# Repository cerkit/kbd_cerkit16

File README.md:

# kbd_cerkit16
 16 Key macro pad

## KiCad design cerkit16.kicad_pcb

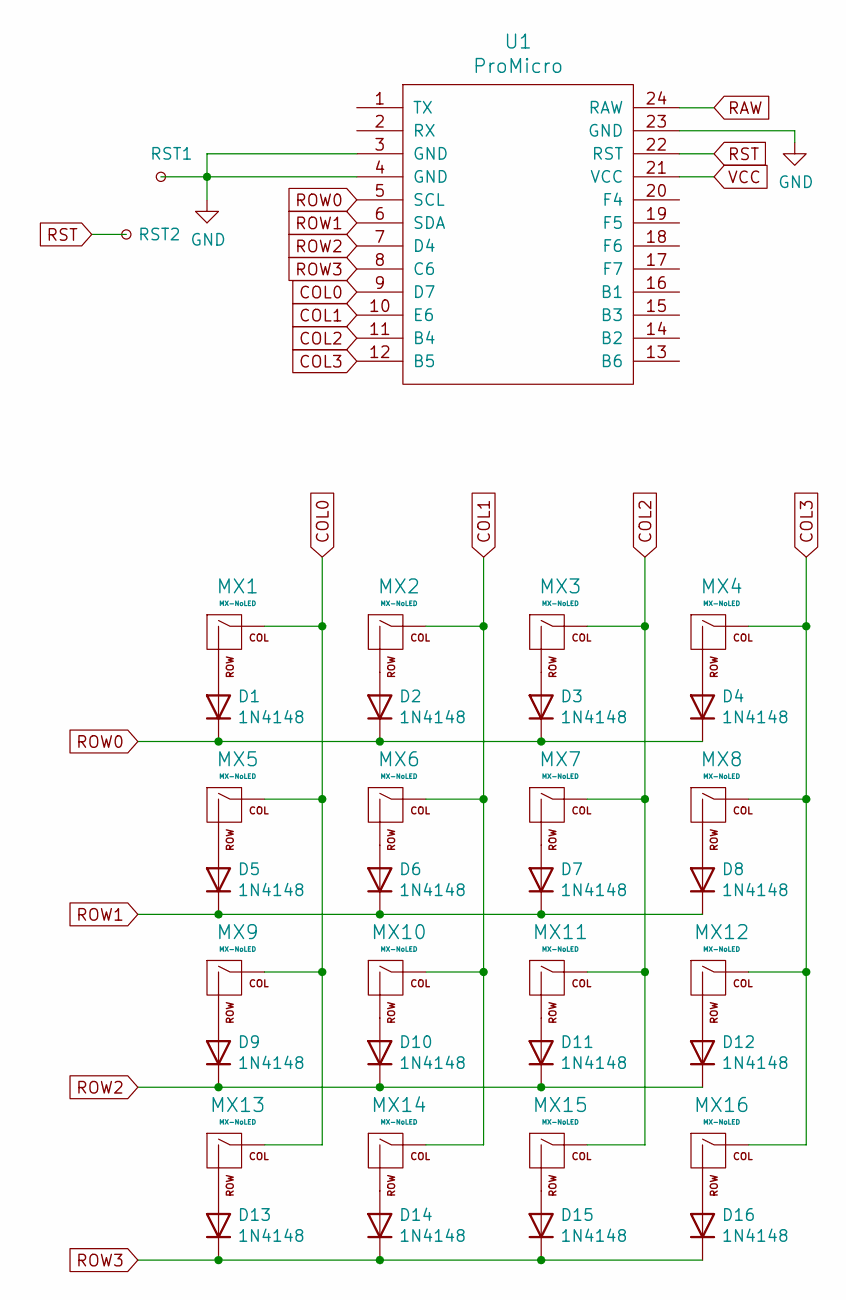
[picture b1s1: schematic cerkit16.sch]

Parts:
D1, D2, D3, D4, D5, D6, D7, D8, D9, D10, D11, D12, D13, D14, D15, D16: 1N4148; D_DO-35_SOD27_P7.62mm_Horizontal
MX1, MX2, MX3, MX4, MX5, MX6, MX7, MX8, MX9, MX10, MX11, MX12, MX13, MX14, MX15, MX16: MX-NoLED; MXOnly-1U-NoLED
RST1, RST2: TestPoint_Small; TestPoint_Pad_1.5x1.5mm
U1: ProMicro

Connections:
COL0: MX1.1 (COL), MX5.1 (COL), MX9.1 (COL), MX13.1 (COL), U1.9 (D7)
COL1: MX2.1 (COL), MX6.1 (COL), MX10.1 (COL), MX14.1 (COL), U1.10 (E6)
COL2: MX3.1 (COL), MX7.1 (COL), MX11.1 (COL), MX15.1 (COL), U1.11 (B4)
COL3: MX4.1 (COL), MX8.1 (COL), MX12.1 (COL), MX16.1 (COL), U1.12 (B5)
GND: RST1.1, U1.3 (GND), U1.4 (GND), U1.23 (GND)
unnamed: D1.2 (A), MX1.2 (ROW)
unnamed: D2.2 (A), MX2.2 (ROW)
unnamed: D3.2 (A), MX3.2 (ROW)
unnamed: D4.2 (A), MX4.2 (ROW)
unnamed: D5.2 (A), MX5.2 (ROW)
unnamed: D6.2 (A), MX6.2 (ROW)
unnamed: D7.2 (A), MX7.2 (ROW)
unnamed: D8.2 (A), MX8.2 (ROW)
unnamed: D9.2 (A), MX9.2 (ROW)
unnamed: D10.2 (A), MX10.2 (ROW)
unnamed: D11.2 (A), MX11.2 (ROW)
unnamed: D12.2 (A), MX12.2 (ROW)
unnamed: D13.2 (A), MX13.2 (ROW)
unnamed: D14.2 (A), MX14.2 (ROW)
unnamed: D15.2 (A), MX15.2 (ROW)
unnamed: D16.2 (A), MX16.2 (ROW)
RAW: U1.24 (RAW)
ROW0: D1.1 (K), D2.1 (K), D3.1 (K), D4.1 (K), U1.5 (SCL)
ROW1: D5.1 (K), D6.1 (K), D7.1 (K), D8.1 (K), U1.6 (SDA)
ROW2: D9.1 (K), D10.1 (K), D11.1 (K), D12.1 (K), U1.7 (D4)
ROW3: D13.1 (K), D14.1 (K), D15.1 (K), D16.1 (K), U1.8 (C6)
RST: RST2.1, U1.22 (RST)
VCC: U1.21 (VCC)

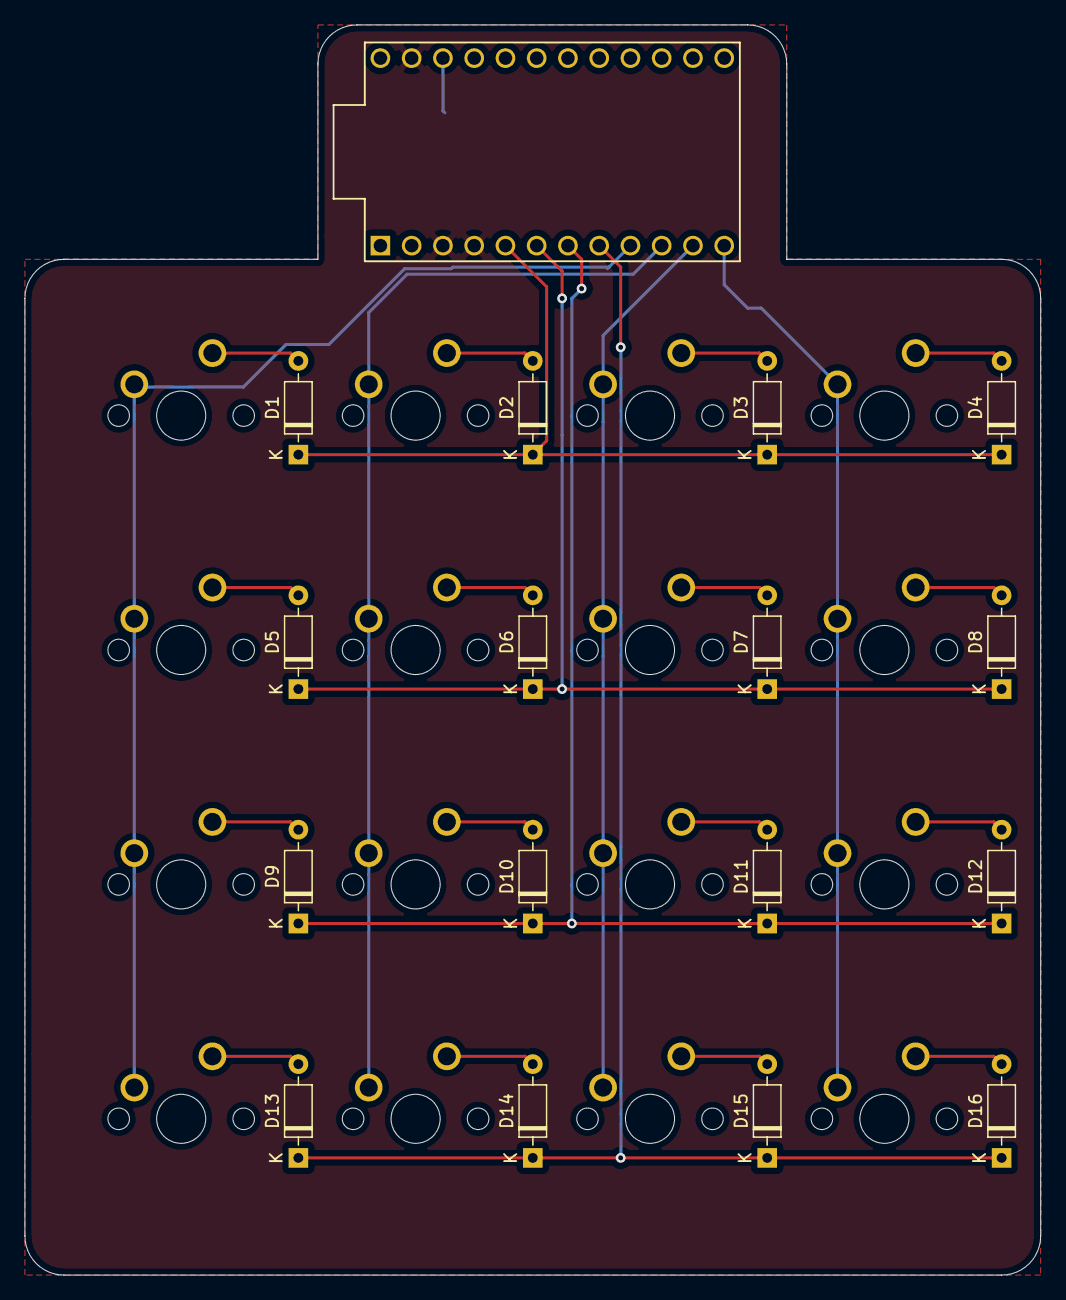
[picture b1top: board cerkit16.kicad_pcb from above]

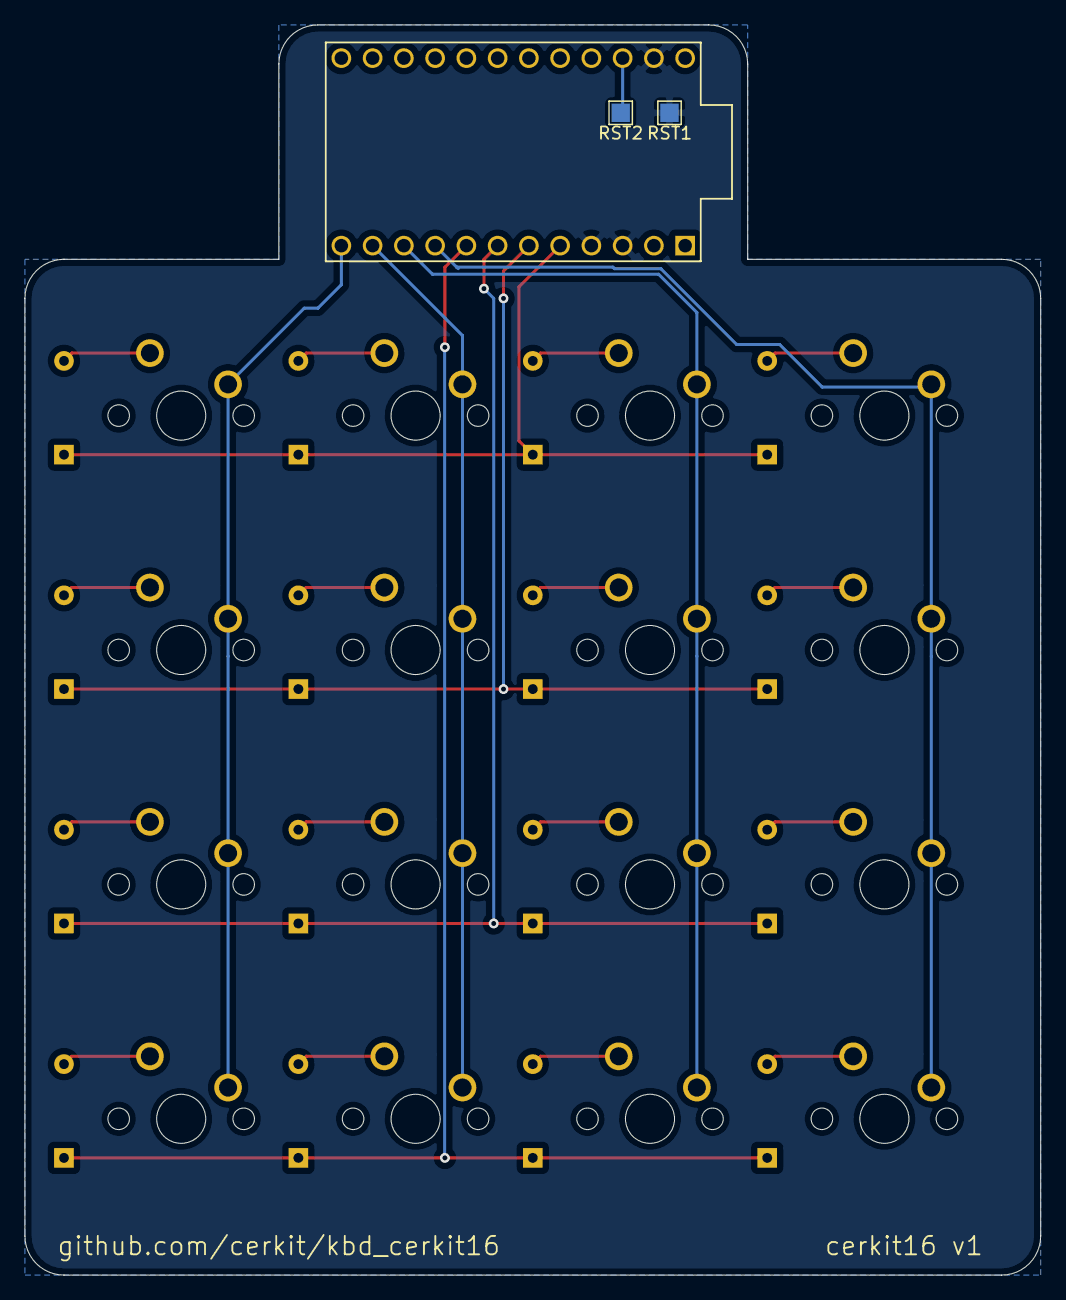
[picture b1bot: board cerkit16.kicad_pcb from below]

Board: 2 copper layers, 82.5 x 101.6 mm, 35 parts (2 on the bottom side), 26 nets.

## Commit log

2020-05-26 Added Pro Micro submodule
2020-05-26 Added keyboard submodules
2020-05-26 worked on PCB
2020-05-26 updated PCB
2020-05-26 cleaned up PCB
2020-05-27 Added edge cuts with curved corners
2020-05-27 reduced the board size
2020-05-27 added gerbers
2020-06-07 moved the controller to the top of the board
2020-06-07 added back copper image
